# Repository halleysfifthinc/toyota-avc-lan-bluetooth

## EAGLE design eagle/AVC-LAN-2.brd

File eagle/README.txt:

These files are part of toyota-avc-lan-bluetooth.
    toyota-avc-lan-bluetooth is free software and open hardware design: 
    you can redistribute it and/or modify it under the terms of the Lesser
    GNU General Public License as published by the Free Software Foundation,
    either version 3 of the License, or (at your option) any later version.

    toyota-avc-lan-bluetooth is distributed in the hope that it will be useful,
    but WITHOUT ANY WARRANTY; without even the implied warranty of
    MERCHANTABILITY or FITNESS FOR A PARTICULAR PURPOSE.  See the
    Lesser GNU General Public License for more details.

    You should have received a copy of the Lesser GNU General Public License
    along with toyota-avc-lan-bluetooth.  If not, see <http://www.gnu.org/licenses/>.

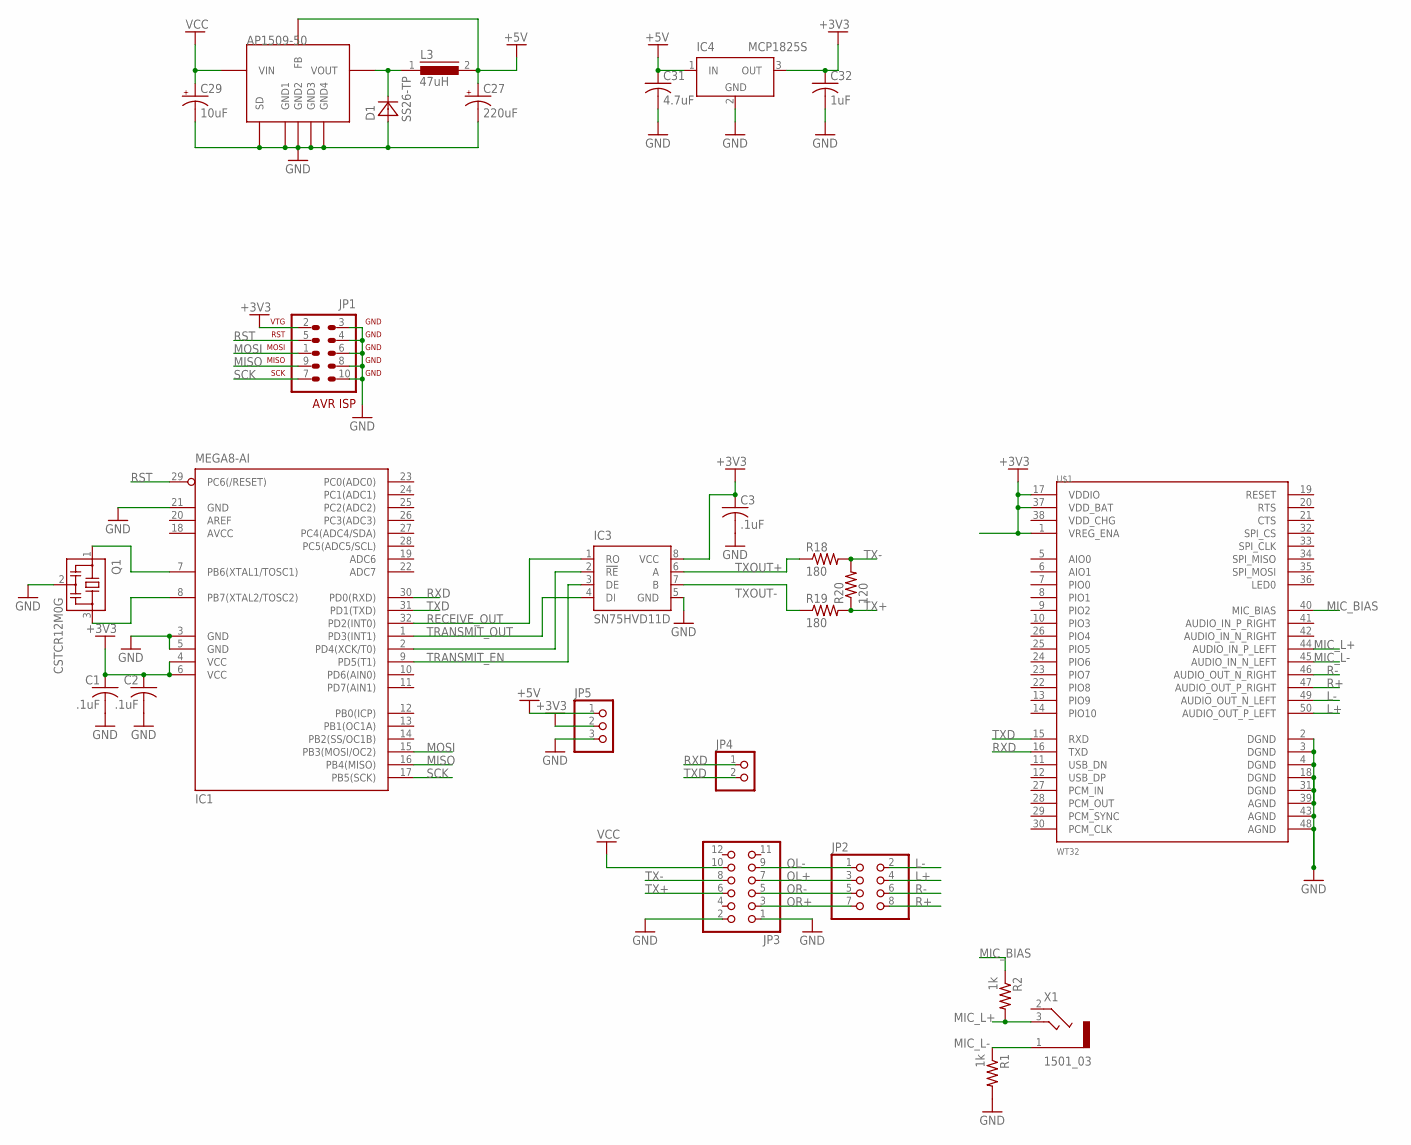
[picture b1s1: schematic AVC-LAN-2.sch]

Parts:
C1, C2, C3: .1uF; C0603
C27: 220uF; D/7343-31W
C29: 10uF; C/6032-28R
C31: 4.7uF; C0603
C32: 1uF; C0603
D1: SS26-TP; SMA
IC1: MEGA8-AI; TQFP32-08
IC3: SN75HVD11D; SOIC8
IC4: MCP1825S; SOT223
JP1: AVR-ISP-10R
JP2: PINHD-2X4; 2X04
JP3: PINHD-2X6/90; 2X06/90
JP4: PINHD-1X2; 1X02
JP5: PINHD-1X3; 1X03
L3: 47uH; DR125
Q1: CSTCR12M0G; CSTER12M; MPN CSTCC12M0
R1, R2: 1k; R0603
R18, R19: 180; R0603
R20: 120; R0603
U$1: WT32
U$5: AP1509-50; SOP-8L
X1: 1501_03

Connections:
+3V3: C1.1, C2.1, C3.1, C32.1, IC1.4 (VCC), IC1.6 (VCC), IC3.8 (VCC), IC4.3 (OUT), JP1.2, JP5.2, U$1.1 (VREG_ENA), U$1.17 (VDDIO), U$1.37 (VDD_BAT)
+5V: C27.+, C31.1, IC4.1 (IN), JP5.1, L3.2, U$5.P$3 (FB)
AVCC: IC1.18 (AVCC)
GND: C1.2, C2.2, C3.2, C27.-, C29.-, C31.2, C32.2, D1.A, IC1.3 (GND), IC1.5 (GND), IC1.21 (GND), IC3.5 (GND), IC4.2 (GND), IC4.4 (GND), JP1.3, JP1.4, JP1.6, JP1.8, JP1.10, JP3.1, JP3.2, JP5.3, Q1.2, R1.2, U$1.2 (DGND), U$1.3 (DGND), U$1.4 (DGND), U$1.18 (DGND), U$1.31 (DGND), U$1.39 (AGND), U$1.43 (AGND), U$1.48 (AGND), U$5.P$4 (SD), U$5.P$5 (GND1), U$5.P$6 (GND2), U$5.P$7 (GND3), U$5.P$8 (GND4)
L+: JP2.4, U$1.50 (AUDIO_OUT_P_LEFT)
L-: JP2.2, U$1.49 (AUDIO_OUT_N_LEFT)
MIC_BIAS: R2.1, U$1.40 (MIC_BIAS)
MIC_L+: R2.2, U$1.44 (AUDIO_IN_P_LEFT), X1.3
MIC_L-: R1.1, U$1.45 (AUDIO_IN_N_LEFT), X1.1
MISO: IC1.16 (PB4(MISO)), JP1.9
MOSI: IC1.15 (PB3(MOSI/OC2)), JP1.1
unnamed: IC1.2 (PD4(XCK/T0)), IC3.2 (!RE)
unnamed: IC1.7 (PB6(XTAL1/TOSC1)), Q1.1
unnamed: IC1.8 (PB7(XTAL2/TOSC2)), Q1.3
OL+: JP2.3, JP3.7
OL-: JP2.1, JP3.9
OR+: JP2.7, JP3.3
OR-: JP2.5, JP3.5
R+: JP2.8, U$1.47 (AUDIO_OUT_P_RIGHT)
R-: JP2.6, U$1.46 (AUDIO_OUT_N_RIGHT)
RECEIVE_OUT: IC1.32 (PD2(INT0)), IC3.1 (RO)
RST: IC1.29 (PC6(/RESET)), JP1.5
RXD: IC1.30 (PD0(RXD)), JP4.1, U$1.16 (TXD)
SCK: IC1.17 (PB5(SCK)), JP1.7
TRANSMIT_EN: IC1.9 (PD5(T1)), IC3.3 (DE)
TRANSMIT_OUT: IC1.1 (PD3(INT1)), IC3.4 (DI)
TX+: JP3.6, R19.2, R20.1
TX-: JP3.8, R18.2, R20.2
TXD: IC1.31 (PD1(TXD)), JP4.2, U$1.15 (RXD)
TXOUT+: IC3.6 (A), R18.1
TXOUT-: IC3.7 (B), R19.1
VCC: C29.+, JP3.10, U$5.P$1 (VIN)
VOUT: D1.C, L3.1, U$5.P$2 (VOUT)

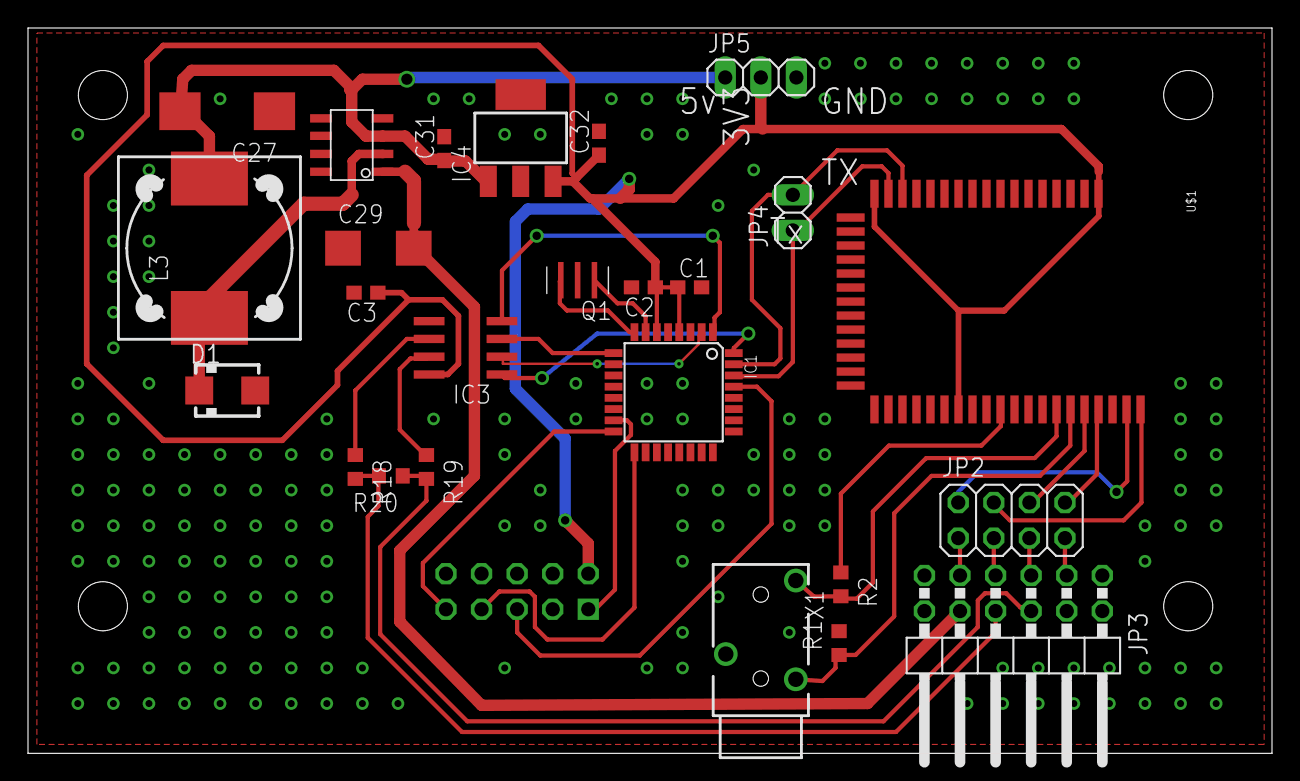
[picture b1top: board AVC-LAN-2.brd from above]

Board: 2 copper layers, 88.8 x 51.8 mm, 26 parts (1 on the bottom side), 32 nets.

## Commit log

2012-07-18 First commit, Working Version
2012-07-18 Small update to .gitignore and added correct RS485 driver part
2012-07-18 Added Licence info
2013-06-22 Updated code changes and improvments
2015-07-28 Migrating wiki contents from Google Code

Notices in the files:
parts and their libraries:
SparkFun: Licensing: CC v3.0 Share-Alike You are welcome to use this library for commercial purposes.
supply0: Copyright (C) 2007, Bob Starr
